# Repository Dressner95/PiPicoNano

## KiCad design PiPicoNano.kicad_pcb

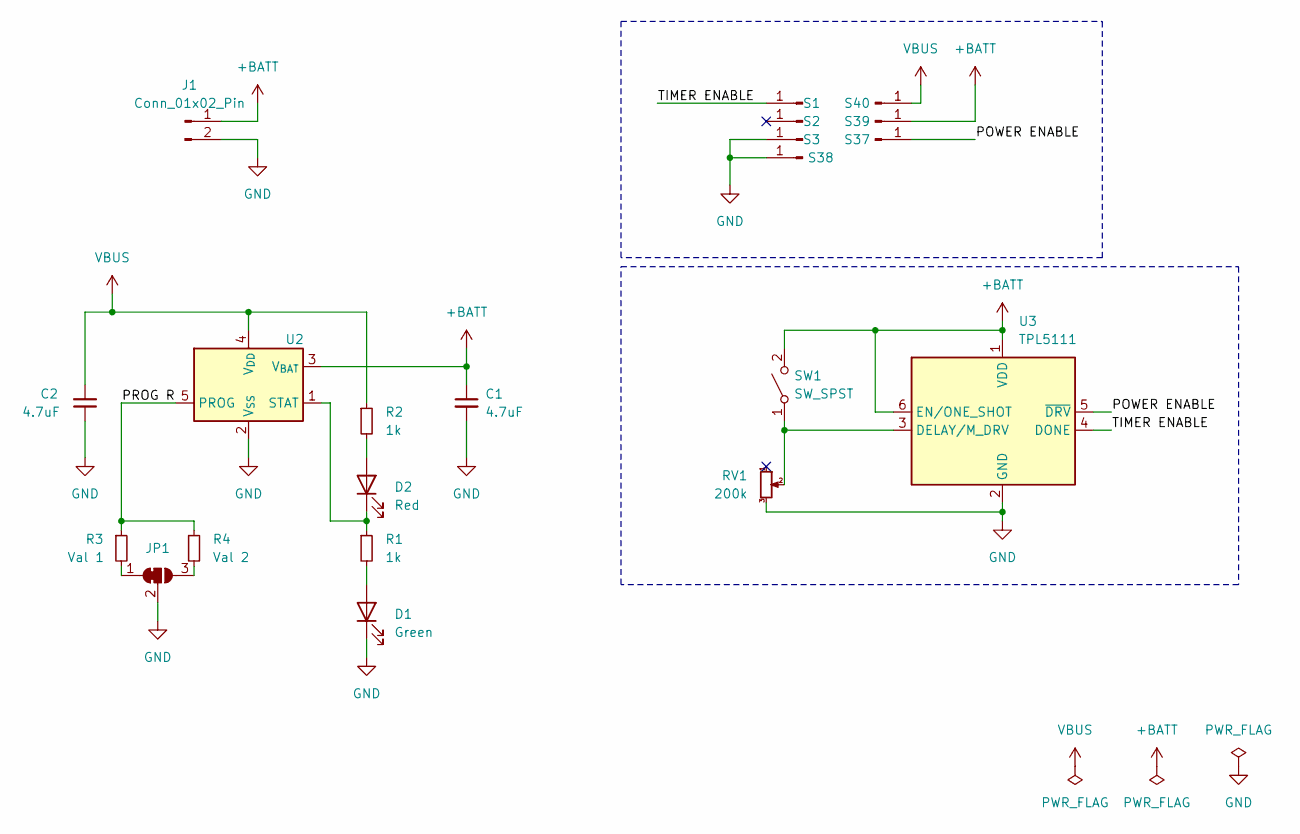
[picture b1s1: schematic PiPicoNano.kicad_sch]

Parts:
C1, C2: 4.7uF; C_0603_1608Metric_Pad1.08x0.95mm_HandSolder
D1: Green; LED_0603_1608Metric
D2: Red; LED_0603_1608Metric
J1: Conn_01x02_Pin; JST_PH_S2B-PH-SM4-TB_1x02-1MP_P2.00mm_Horizontal
JP1: SolderJumper_3_Bridged12; SolderJumper-3_P1.3mm_Bridged12_RoundedPad1.0x1.5mm_NumberL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
R1, R2: 1k; R_0603_1608Metric_Pad0.98x0.95mm_HandSolder
R3: Val 1; R_0603_1608Metric_Pad0.98x0.95mm_HandSolder
R4: Val 2; R_0603_1608Metric_Pad0.98x0.95mm_HandSolder
RV1: 200k; Potentiometer_Bourns_TC33X_Vertical
S1, S2, S3, S37, S38, S39, S40: Conn_01x01_Pin; 7305
SW1: SW_SPST; SW_SPST_B3U-1000P
U2: MCP73831-2-OT; SOT-23-5
U3: TPL5111; SOT-23-6

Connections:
+BATT: C1.1, J1.1, J1.MP, S39.1, SW1.2 (B), U2.3 (V_{BAT}), U3.1 (VDD), U3.6 (EN/ONE_SHOT)
/POWER ENABLE: S37.1, U3.5 (~DRV)
/PROG R: R3.1, R4.1, U2.5 (PROG)
/TIMER ENABLE: S1.1, U3.4 (DONE)
GND: C1.2, C2.1, D1.1 (K), J1.2, JP1.2 (C), RV1.3, S3.1, S38.1, U2.2 (V_{SS}), U3.2 (GND)
unnamed: D1.2 (A), R1.2
unnamed: D2.2 (A), R2.2
unnamed: D2.1 (K), R1.1, U2.1 (STAT)
unnamed: JP1.1 (A), R3.2
unnamed: JP1.3 (B), R4.2
unnamed: RV1.2, SW1.1 (A), U3.3 (DELAY/M_DRV)
VBUS: C2.2, R2.1, S40.1, U2.4 (V_{DD})

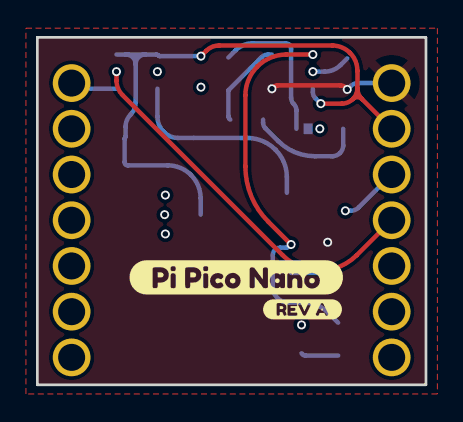
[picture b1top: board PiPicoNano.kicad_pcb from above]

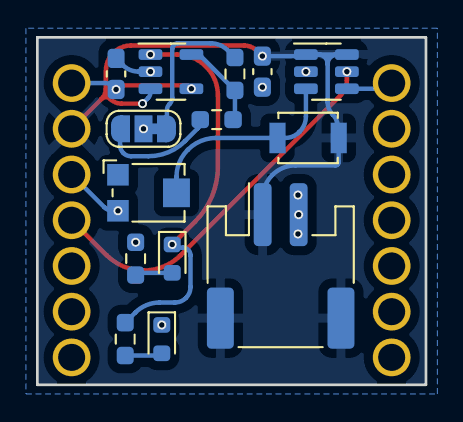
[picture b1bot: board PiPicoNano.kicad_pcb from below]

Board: 4 copper layers, 21.6 x 19.3 mm, 23 parts (14 on the bottom side), 12 nets.

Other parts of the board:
kibuzzard-64F5148F: G***; kibuzzard-64F5148F
kibuzzard-64F51413: G***; kibuzzard-64F51413

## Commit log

2023-09-04 Commit for REV A
2023-09-04 Adjusted file organization
